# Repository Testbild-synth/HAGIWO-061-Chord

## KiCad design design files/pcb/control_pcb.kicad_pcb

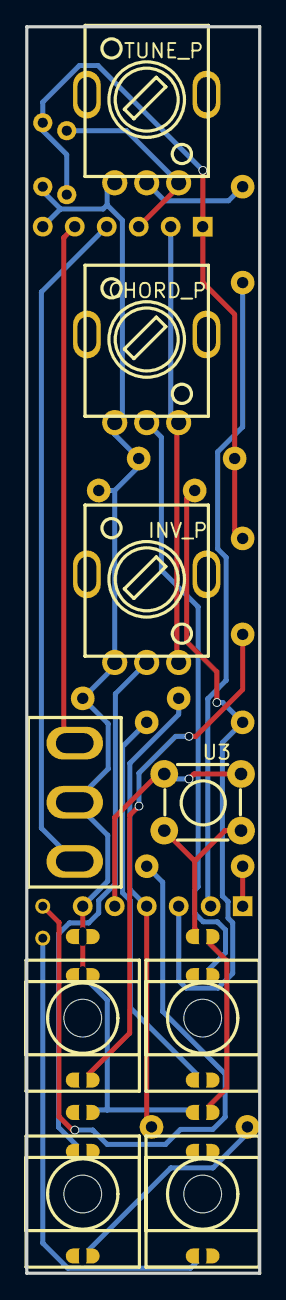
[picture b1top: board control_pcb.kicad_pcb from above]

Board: 2 copper layers, 18.5 x 99.0 mm, 22 parts (0 on the bottom side), 19 nets.

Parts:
C5: 4.7n; RAD-0.1
CHORD_P: 10k; R09-5KΩ
D1, D7: B43; DIODE
H1, H2: HDR-F-2.54_1x6; HDR-F-2.54_1X6
INV_P: 10k; R09-5KΩ
J1: CHORD_IN; THONKICONN_1
J2: INV_IN; THONKICONN_1
J3: CV_IN; THONKICONN_1
J4: OUT; THONKICONN_1
R1: 3.3k; R_AXIAL-0.3
R2, R6: 180k; R_AXIAL-0.3
R3, R5: 330k; R_AXIAL-0.3
R4: 1k; R_AXIAL-0.3
R10: 330; R_AXIAL-0.3
R19: 1.8k; R_AXIAL-0.3
S5: SPDT; TOGGLE SWITCH SPDT RED 3 PIN ON-OFF-ON 3 SPDT SMALL AC 6A/1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
TUNE_P: 10k; R09-5KΩ
U3: WAVE; PUSHBUTTON

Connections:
3V3: D7.2, H1.3, TUNE_P.3
5V: CHORD_P.3, H1.2, INV_P.3
C5_2: C5.2, R10.2
CHORD: H2.3, R2.1, R3.1
CHORD_P_2: CHORD_P.2, J1.2
CVIN: D1.2, D7.1, H1.1, R1.1, R19.1
GND: CHORD_P.1, D1.1, H1.6, H2.6, INV_P.1, J1.1, J2.1, J3.1, J3.2, J4.1, R1.2, R3.2, R5.2, S5.2, TUNE_P.1, U3.3, U3.4
INV: H2.4, R5.1, R6.1
J1_3: J1.3, R2.2
J2_2: INV_P.2, J2.2
J3_3: J3.3, R19.2
J4_3: C5.1, J4.3
MODE_1: H1.4, S5.3
MODE_2: H1.5, S5.1
OUT_BUF: H2.1, R10.1
R6_2: J2.3, R6.2
TUNE: H2.2, R4.1
TUNE_P_2: R4.2, TUNE_P.2
WAVE: H2.5, U3.1, U3.2

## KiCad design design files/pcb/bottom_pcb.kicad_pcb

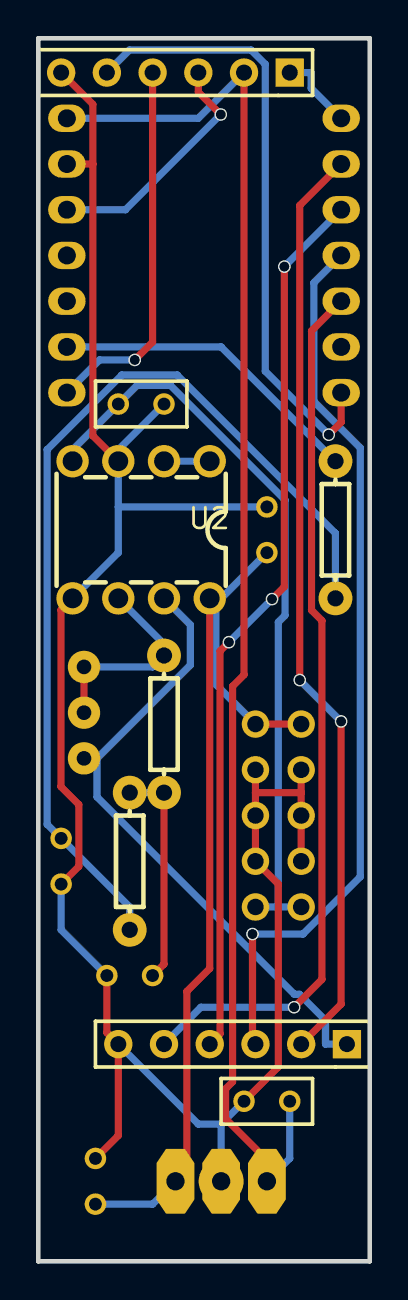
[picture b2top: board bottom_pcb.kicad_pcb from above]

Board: 2 copper layers, 18.4 x 67.9 mm, 16 parts (0 on the bottom side), 18 nets.

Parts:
C1, C2, C6, C7: 100n; RAD-0.1
C3, C4: 10n; RAD-0.1
H1, H2: HDR-F-2.54_1x6; HDR-F-2.54_1X6
P1: POWER; EURORACK SHROUDED POWER 10 PIN
R7, R8: 1k; R_AXIAL-0.3
R9: 10k; TRIMPOT-ELETROCURSOS-FOOTPRINT
R11: 4.7k; R_AXIAL-0.3
U1: rp2040_xiao; RP2040_XIAO
U2: TL072IP; PDIP-8_L10.2-W5.9-P2.54-LS7.6-BL
U4: 7805

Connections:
3V3: H1.3, U1.5
5V: C1.2, H1.2, U1.7, U4.3
12V: C2.2, C7.2, P1.1, U2.8, U4.1
-12V: C6.2, P1.5, U2.4
C4_2: C4.2, R8.2, R11.1
CHORD: H2.3, U1.11
CVIN: H1.1, U1.8
GND: C1.1, C2.1, C3.1, C4.1, C6.1, C7.1, H1.6, H2.6, P1.2, P1.3, P1.4, U1.6, U2.3, U2.5, U4.2
INV: H2.4, U1.10
MODE_1: H1.4, U1.1
MODE_2: H1.5, U1.14
OUT: R7.1, U1.2
OUT_BUF: H2.1, R9.3, U2.7
R7_2: C3.2, R7.2, R8.1
TUNE: H2.2, U1.9
U2_1: U2.1, U2.2
U2_6: R9.1, R9.2, R11.2, U2.6
WAVE: H2.5, U1.12

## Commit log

2024-09-01 initial file upload
2024-09-01 upload arduino sketch
